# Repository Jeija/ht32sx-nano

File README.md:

# HT Micron HT32SX Development Board

This repository contains the KiCad board design files and the [PDF schematic](ht32sx-nano.pdf).

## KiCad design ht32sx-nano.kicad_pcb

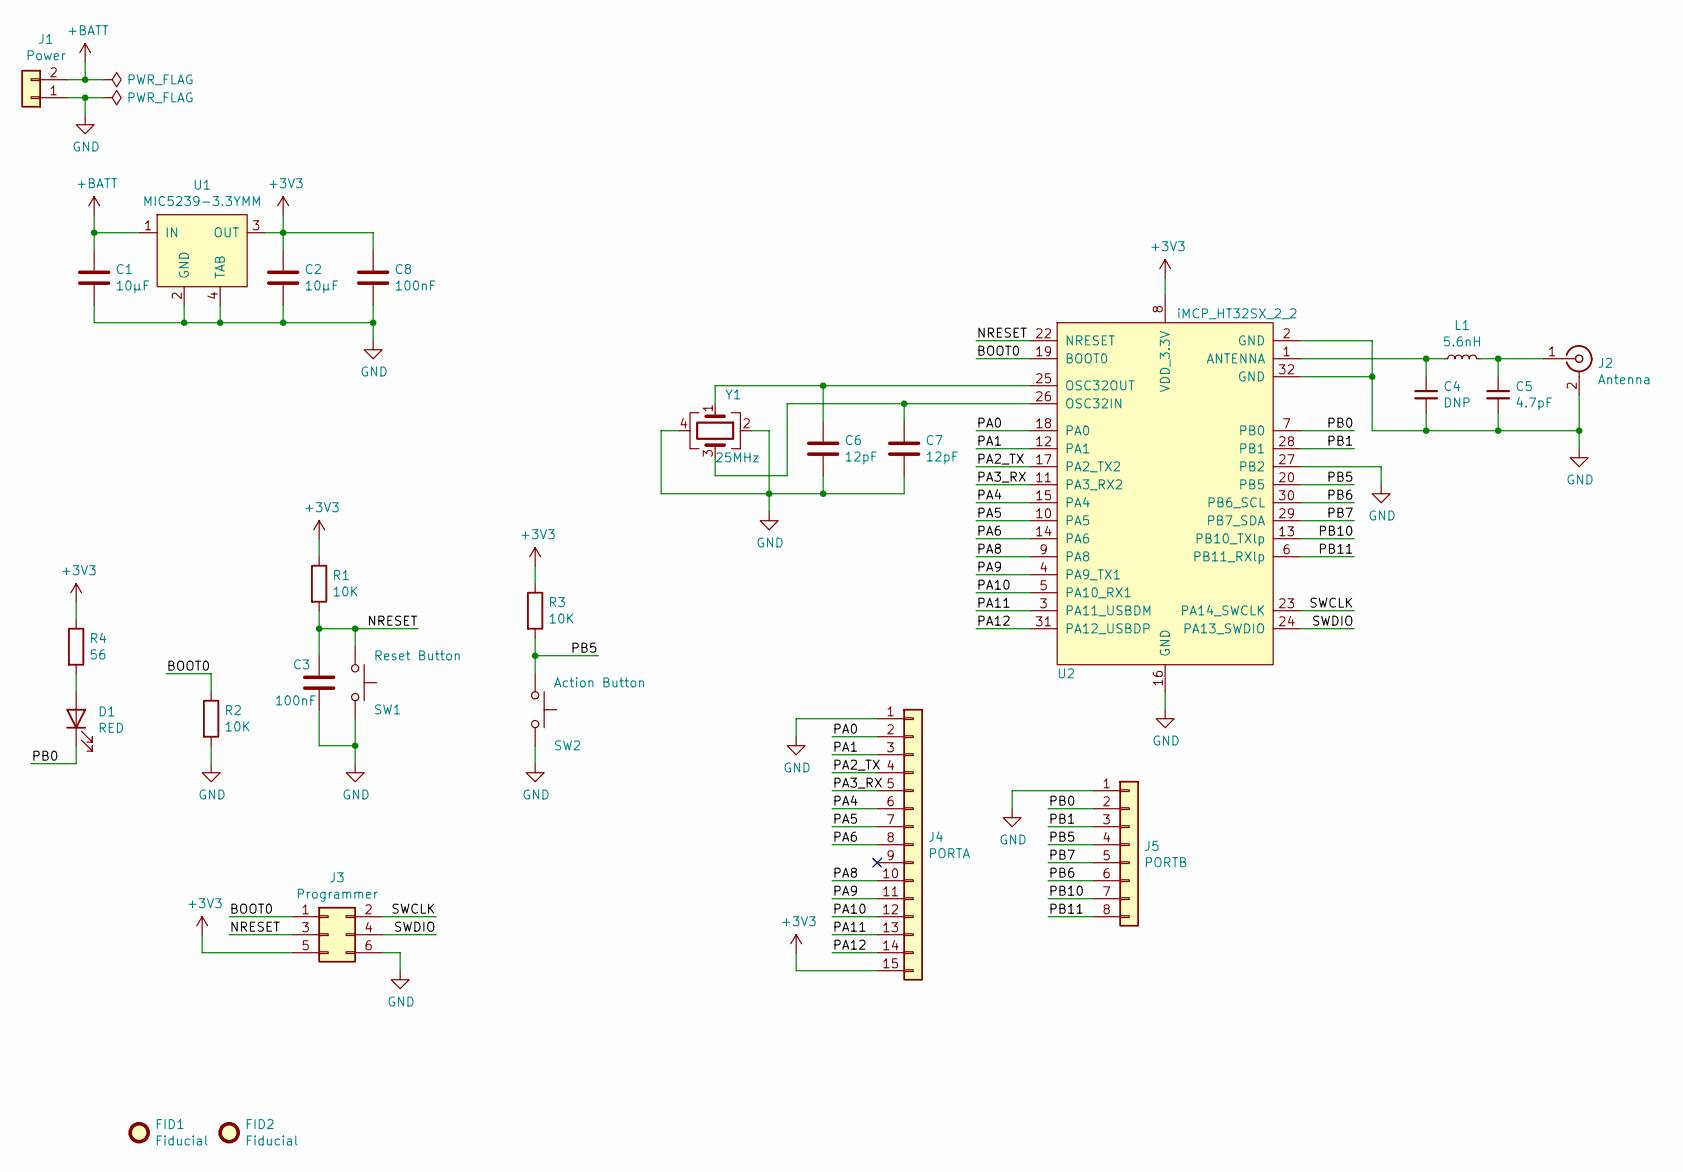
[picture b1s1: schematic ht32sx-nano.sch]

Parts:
C1, C2: 10µF; C_0603_1608Metric
C3, C8: 100nF; C_0603_1608Metric
C4: DNP; C_0201_0603Metric
C5: 4.7pF; C_0201_0603Metric
C6, C7: 12pF; C_0603_1608Metric
D1: RED; LED_0603_1608Metric
FID1, FID2: Fiducial; Fiducial_0.75mm_Mask1.5mm
J1: Power; PinHeader_1x02_P2.54mm_Vertical
J2: Antenna; SMA_Amphenol_132289_EdgeMount
J3: Programmer; PinHeader_2x03_P2.54mm_Vertical
J4: PORTA; PinHeader_1x15_P2.54mm_Vertical
J5: PORTB; PinHeader_1x08_P2.54mm_Vertical
L1: 5.6nH; L_0402_1005Metric
R1, R2, R3: 10K; R_0603_1608Metric
R4: 56; R_0603_1608Metric
SW1: Reset Button; SW_SPST_CK_RS282G05A3
SW2: Action Button; SW_SPST_CK_RS282G05A3
U1: MIC5239-3.3YMM; SOT-223
U2: iMCP_HT32SX_2_2; iMCP_HT32SX
Y1: 25MHz; Crystal_SMD_3225-4Pin_3.2x2.5mm

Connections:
+3V3: C2.1, C8.1, J3.5, J4.15, R1.1, R3.1, R4.1, U1.3 (OUT), U2.8 (VDD_3.3V)
+BATT: C1.1, J1.2, U1.1 (IN)
/BOOT0: J3.1, R2.1, U2.19 (BOOT0)
/NRESET: C3.1, J3.3, R1.2, SW1.1, U2.22 (NRESET)
/PA0: J4.2, U2.18 (PA0)
/PA1: J4.3, U2.12 (PA1)
/PA2_TX: J4.4, U2.17 (PA2_TX2)
/PA3_RX: J4.5, U2.11 (PA3_RX2)
/PA4: J4.6, U2.15 (PA4)
/PA5: J4.7, U2.10 (PA5)
/PA6: J4.8, U2.14 (PA6)
/PA8: J4.10, U2.9 (PA8)
/PA9: J4.11, U2.4 (PA9_TX1)
/PA10: J4.12, U2.5 (PA10_RX1)
/PA11: J4.13, U2.3 (PA11_USBDM)
/PA12: J4.14, U2.31 (PA12_USBDP)
/PB0: D1.1 (K), J5.2, U2.7 (PB0)
/PB1: J5.3, U2.28 (PB1)
/PB5: J5.4, R3.2, SW2.1, U2.20 (PB5)
/PB6: J5.6, U2.30 (PB6_SCL)
/PB7: J5.5, U2.29 (PB7_SDA)
/PB10: J5.7, U2.13 (PB10_TXlp)
/PB11: J5.8, U2.6 (PB11_RXlp)
/SWCLK: J3.2, U2.23 (PA14_SWCLK)
/SWDIO: J3.4, U2.24 (PA13_SWDIO)
GND: C1.2, C2.2, C3.2, C4.2, C5.2, C6.2, C7.2, C8.2, J1.1, J2.2 (Ext), J3.6, J4.1, J5.1, R2.2, SW1.2, SW2.2, U1.2 (GND), U1.4 (TAB), U2.2 (GND), U2.16 (GND), U2.21 (GND), U2.27 (GND), U2.32 (GND), U2.33 (GND), Y1.2, Y1.4
unnamed: C4.1, L1.1, U2.1 (ANTENNA)
unnamed: C5.1, J2.1 (In), L1.2
unnamed: C6.1, U2.25 (OSC32OUT), Y1.1
unnamed: C7.1, U2.26 (OSC32IN), Y1.3
unnamed: D1.2 (A), R4.2

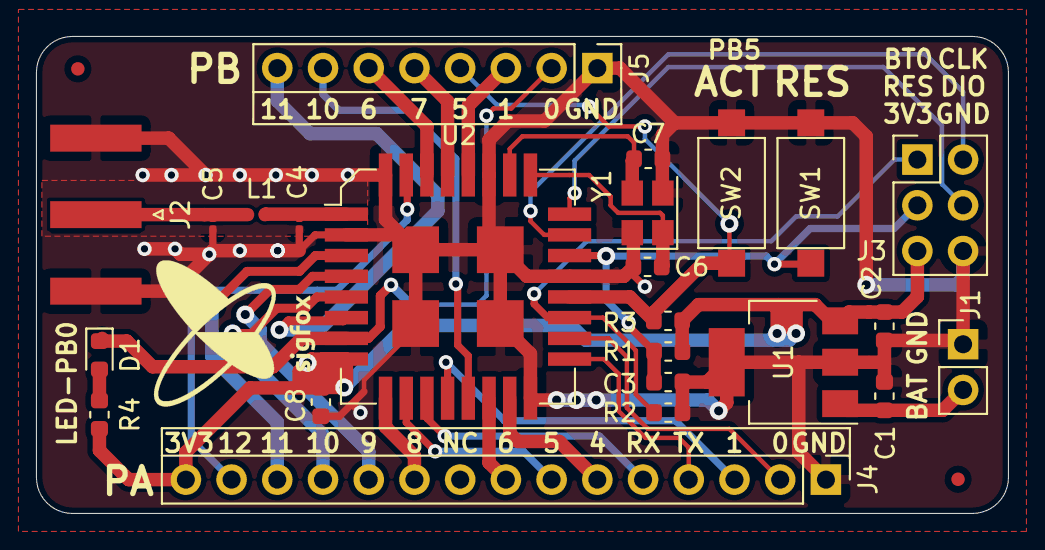
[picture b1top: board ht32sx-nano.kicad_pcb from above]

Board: 2 copper layers, 54.0 x 26.5 mm, 26 parts (0 on the bottom side), 31 nets.

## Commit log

2020-08-27 Initial upload
2020-08-27 Add README and picture
